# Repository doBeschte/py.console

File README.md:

# py.console
A gaming console based on a Raspberry Pi 5 and python games with 5 bluetooth-controllers
I designed the 3D-printed parts in Fusion360, the schematics and the PCB in KiCAD.

# HARDWARE

## CONSOLE

The console is based on a Raspberry Pi 5. The 3D-printed housing (12cm x 12cm) includes two parts. The main part holds all the components and electronics.
The top view looks like this:

On the left side of this picture the Raspberry Pi will be mounted using four pieces that fit into its mounting holes. The HDMI-Ports and the USB-C-Ports are accessible from the back side of the console.
On the sides I designed some holes for the air outlet of the device. 

On the front are two holes for a USB port and a boot push button. 
The USB port is connected to the USB port of the Raspberry Pi. It will be used to connect a USB stick with the .py game files.
The wires of the push button are connected to the two pins next to the battery connector on the Raspberry Pi to act like the integrated button.
The button has an integrated LED that is connected to GPIO13 with a resistor in series to be enabled when the device is operating.
An active buzzer is connected to GPIO18 to make a sound when booting or starting a game. It is placed in the hole of the case.

The other housing part is the top cover.

It is mounted with two screws on the front and round pieces that fit into holes in the main part at the back.

I will use the Raspberry Pi active cooler that takes air through the holes in the top cover.

https://github.com/user-attachments/assets/2c3ed64f-fc42-457b-9e3d-2fc4b27291a0

*This video shows how the mounting will work*

## CONTROLLERS

The controllers are more complicated as they are smaller and include more components.
I build five of them because a lot of things are shipped in five or ten, including PCBs, Joysticks, buttons, batteries etc. .

The rendering doesn't include the joystick because I don't print it by myself.

The microcontroller is a XIAO-ESP32-C3 that has BLE and a battery charger and it is small. Its USB-C port is the charging port of my controller.

At the left side is a tipical thumb joystick and at the right side two buttons. They are connected to inputs on the ESP32 and GND.
Around the PCB are 20 "PL9823" LEDs. They need 5 volts which the ESP32 doesn't deliver. So, I use a little boost converter from the battery cell to five volts and a 74125 level shifter (with a 330Ω resistor) for the data. A MOSFET turnes the boost converter off when the ESP32 is in DeepSleep.
Two capacitors deliver high current for the LEDs for a short time.
The battery voltage is measured by splitting it in half using two resistors 1MΩ

The device is 12cm x 5cm, rounded at the sides and around 26mm thick. The case is made like the one of the console, but the cover is at the opposite side. The PCB is held between these two parts.
The main part holds the battery in the middle and the "keycaps" at the right side OF THE DEVICE.

The "keycaps" just fit into their holes and have a margin to prevent falling out.

The cover is screwed into the main case at the sides. It holds the PCB at the edges, under the joystick and under the keys for pressure, leaving a bit of space for the solder joints.

The PCB in my Renderings does not already contain all of the parts and some are just visible as pin headers:

The following picture shows the mounted PCB inside the case. It might look wrong at the sides (little space) but it isn't.

## BOM

CONSOLE:

• Raspberry Pi 5, 4GB RAM  -  / 

• Power supply for Pi 5  -  / 

• Raspberry Pi 5 active cooler  -  /

• USB-A port  -  /

• push button, 16mm mounting hole  -  /

• active buzzer, 24mm Ø  -  /

• 330Ω resistor  -  /

• microSD-card  -  /

TOTAL PRICE CONSOLE: / (I will buy everything by myself)

CONTROLLERS:

• 5pcs custom PCB, 112mm*46mm  -  5,16€

• 5pcs Seeed Studio XIAO-ESP32-C3  -  33,33€

• 5pcs thumb joystick  -  0,87€

• 10pcs silent push button, 8*8mm  -  5,62€

• 10pcs LiPo battery, 30mm* 40mm* 5mm  -  16,88€

• 5pcs voltage regulator  -  7,50€

• 5pcs 74125 level shifter  -  5,04€

• 5pcs 330Ω resistor  -  / (I have them)

• 10pcs 1MΩ resistor  -  / (also them :D )

• 10pcs 100nF capacitor  -  0,87€

• 5pcs polarized capacitor  -  0,87€

• 100pcs PL9823 LED  -  5,50€

• 5pcs MOSFET (IRLZ44N)  -  4,60€

TOTAL PRICE 5 CONTROLLERS: 85,55€

# SOFTWARE

## CONSOLE

The console uses the Raspberry Pi Desktop. After booting, a menu appears. It shows python files saved on the external USB stick and uses pygame for the graphics.
The idea behind this project: All of the other software are some python games on a USB stick. I can code them by myself or download them from the internet - as many as I want!

## CONTROLLERS

The controllers are coded in C++ and use ESP32 bleGamepad library. They use DeepSleep to be shut down by pressing the joystick for 5 seconds or by inactivity. Pressing the Joystick will wake the ESP32 up.
The code includes a lot of animations for the LEDs, using fastLED library. The battery level is calculated using the measured battery voltage and a table from the web. It is sent every 20 seconds to the connected device and displayed on the LEDs when starting and if it is under 20%.

# cart screenshots

**Please note that i will only buy the selected items.**

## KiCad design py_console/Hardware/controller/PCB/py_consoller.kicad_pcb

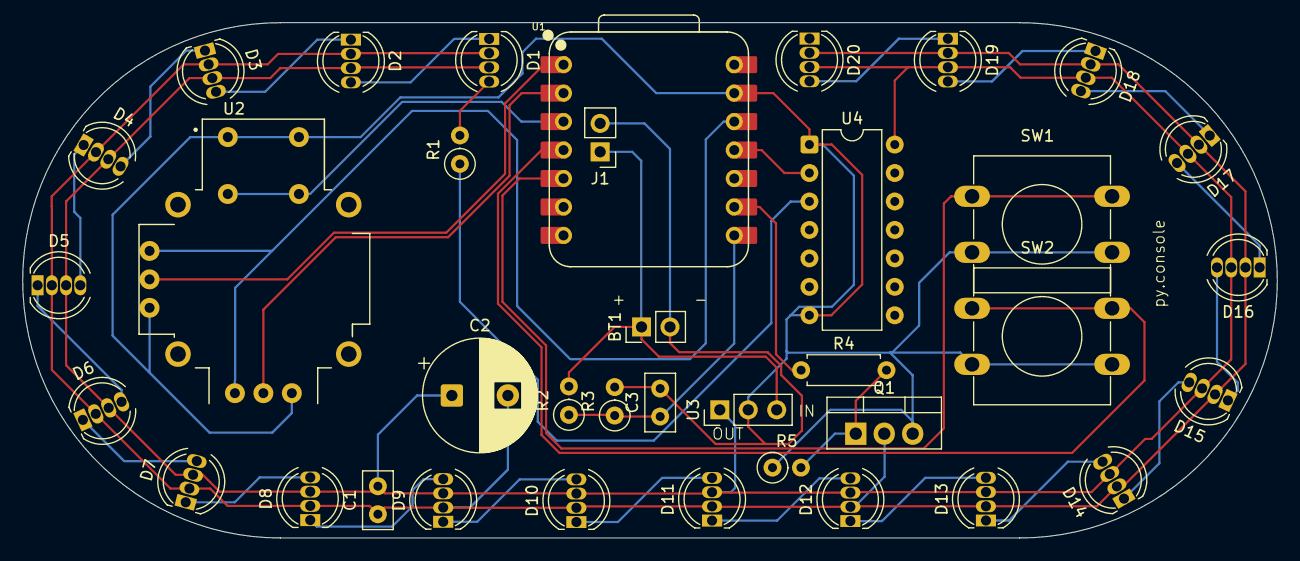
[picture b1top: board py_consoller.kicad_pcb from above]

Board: 2 copper layers, 112.0 x 46.0 mm, 37 parts (0 on the bottom side), 35 nets.

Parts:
BT1: Battery_Cell; PinHeader_1x02_P2.54mm_Vertical
C1, C3: C; C_Disc_D5.0mm_W2.5mm_P2.50mm
C2: C_Polarized; CP_Radial_D10.0mm_P5.00mm
D1, D2, D3, D4, D5, D6, D7, D8, D9, D10, D11, D12, D13, D14, D15, D16, D17, D18, D19, D20: PL9823; LED_D5.0mm-4_RGB
J1: Conn_01x02; PinHeader_1x02_P2.54mm_Vertical
Q1: IRLZ34N; TO-220-3_Vertical
R1: 330Ω; R_Axial_DIN0207_L6.3mm_D2.5mm_P2.54mm_Vertical
R2, R3, R5: R; R_Axial_DIN0207_L6.3mm_D2.5mm_P2.54mm_Vertical
R4: R; R_Axial_DIN0207_L6.3mm_D2.5mm_P7.62mm_Horizontal
SW1, SW2: SW_Push; SW_PUSH-12mm
U1: XIAO ESP32C3; XIAO-ESP32C3-DIP
U2: JOYSTICK_W_BUTTON; XDCR_COM-09032
U3: PinHeader_1x03_P2.54mm_Vertical
U4: 74125; DIP-14_W7.62mm

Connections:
unnamed: BT1.1 (+), J1.1, R2.2, U3.3 (VIN)
unnamed: BT1.2 (-), C3.2, J1.2, Q1.3 (S), R3.2, R5.1, SW1.2, SW2.2, U1.13 (GND), U2.SW1, U2.X3, U2.Y3, U3.2 (GND), U4.1 (EN), U4.7 (GND)
unnamed: D1.4 (DIN), R1.2
unnamed: D1.2 (DO), D2.4 (DIN)
unnamed: C1.1, C2.2, D1.1 (GND), D2.1 (GND), D3.1 (GND), D4.1 (GND), D5.1 (GND), D6.1 (GND), D7.1 (GND), D8.1 (GND), D9.1 (GND), D10.1 (GND), D11.1 (GND), D12.1 (GND), D13.1 (GND), D14.1 (GND), D15.1 (GND), D16.1 (GND), D17.1 (GND), D18.1 (GND), D19.1 (GND), D20.1 (GND), Q1.2 (D)
unnamed: C1.2, C2.1, D1.3 (VDD), D2.3 (VDD), D3.3 (VDD), D4.3 (VDD), D5.3 (VDD), D6.3 (VDD), D7.3 (VDD), D8.3 (VDD), D9.3 (VDD), D10.3 (VDD), D11.3 (VDD), D12.3 (VDD), D13.3 (VDD), D14.3 (VDD), D15.3 (VDD), D16.3 (VDD), D17.3 (VDD), D18.3 (VDD), D19.3 (VDD), D20.3 (VDD), U3.1 (VOUT), U4.14 (VCC)
unnamed: D2.2 (DO), D3.4 (DIN)
unnamed: D3.2 (DO), D4.4 (DIN)
unnamed: D4.2 (DO), D5.4 (DIN)
unnamed: D5.2 (DO), D6.4 (DIN)
unnamed: D6.2 (DO), D7.4 (DIN)
unnamed: D7.2 (DO), D8.4 (DIN)
unnamed: D8.2 (DO), D9.4 (DIN)
unnamed: D9.2 (DO), D10.4 (DIN)
unnamed: D10.2 (DO), D11.4 (DIN)
unnamed: D11.2 (DO), D12.4 (DIN)
unnamed: D12.2 (DO), D13.4 (DIN)
unnamed: D13.2 (DO), D14.4 (DIN)
unnamed: D14.2 (DO), D15.4 (DIN)
unnamed: D15.2 (DO), D16.4 (DIN)
unnamed: D16.2 (DO), D17.4 (DIN)
unnamed: D17.2 (DO), D18.4 (DIN)
unnamed: D18.2 (DO), D19.4 (DIN)
unnamed: D19.2 (DO), D20.4 (DIN)
unnamed: Q1.1 (G), R4.2, R5.2
unnamed: U1.1 (D0), U2.X2 (X_WIPER)
unnamed: U1.2 (D1), U2.Y2 (Y_WIPER)
unnamed: U1.3 (D2), U2.SW2
unnamed: SW2.1, U1.4 (D3)
unnamed: SW1.1, U1.5 (D4)
unnamed: C3.1, R2.1, R3.1, U1.8 (D7)
unnamed: R4.1, U1.9 (D8)
unnamed: U1.11 (D10), U4.2 (D)
unnamed: U1.12 (VCC_3V3), U2.X1, U2.Y1
unnamed: R1.1, U4.3 (O)

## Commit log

2026-01-09 Expand README
    Added detailed description of the console's design and components.
2026-01-09 Enhance README with detailed console and controller info
    Expanded details on the console's design, components, and controllers, including images and specifications.
2026-01-11 Update README with hardware details and BOM
    Added detailed hardware specifications and BOM for the console and controllers.
2026-01-11 Update README with hardware and software details
    Added details about the MOSFET, microSD card, and updated resistor values. Expanded software section to include information about the console and controllers.
2026-01-12 Add prices to BOM components in README
    Updated BOM section with prices for components.
2026-01-15 Revise component list with updated prices and details
    Updated pricing and specifications for components in the README.
2026-01-15 Update PCB dimensions in README
2026-01-15 Enhance README with console and controller details
    Updated README with additional details about the console and controllers, including images, pricing, and software functionality.
2026-01-16 Revise BOM with personal item notes and price updates
    Updated BOM with personal notes and removed prices for some components.
2026-01-16 Revise component prices and personal notes in README
    Updated pricing and personal notes for console and controllers in README.
2026-01-17 Revise BOM prices and remove personal notes
    Updated BOM prices and removed personal notes.
2026-02-03 Refactor menu.py for improved USB handling and game launch
2026-02-11 Include cart screenshots in README
    Added cart screenshots to the README.

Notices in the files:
py_console/Hardware/controller/PCB/py_consoller.kicad_pcb:
© Lenz
